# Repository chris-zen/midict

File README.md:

# midict
Hardware, firmware and software for my home made MIDI controllers

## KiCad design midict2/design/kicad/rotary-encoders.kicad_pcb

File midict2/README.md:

# MIDIct2

## Modules

### Knobs
This is a board with 8 rotary encoders to allow controlling several parameters simultaneously.

### Screen

A TFT HVGA 480x320 3.2" screen to show status to the user.
It will be controlled from software through some protocol MIDI SysEx / OSC.

### Control

This is a board with 2 rotary encoders and 6 buttons.
For controlling pages, devices, parameters, transport, ...

## Roadmap

**Knobs**

- [x] PCB design, assembly and verification
- [ ] Firmware development for the RPi
- [ ] RPi setup: mDNS, AppleMIDI driver, USB-OTG MIDI, ...

**Screen**

- [ ] MIDI/OSC Protocol to control the screen content
- [ ] Firmware to draw the screen from the RPi

**Control**

- [ ] PCB design, assembly and verification
- [ ] Firmware development for the RPi

## Images

* [First try for the rotary encoders with a photosensible dry film that was full of scratches](https://goo.gl/photos/vFz5QZcYP5DqDy86A)
* [Second try with tonner transfer using sheets from a magazinne](https://goo.gl/photos/Drio2UvwJJE7scSj7)
* [My own UV insolator](https://goo.gl/photos/k7TKoiVqc2WFZSGJ9)

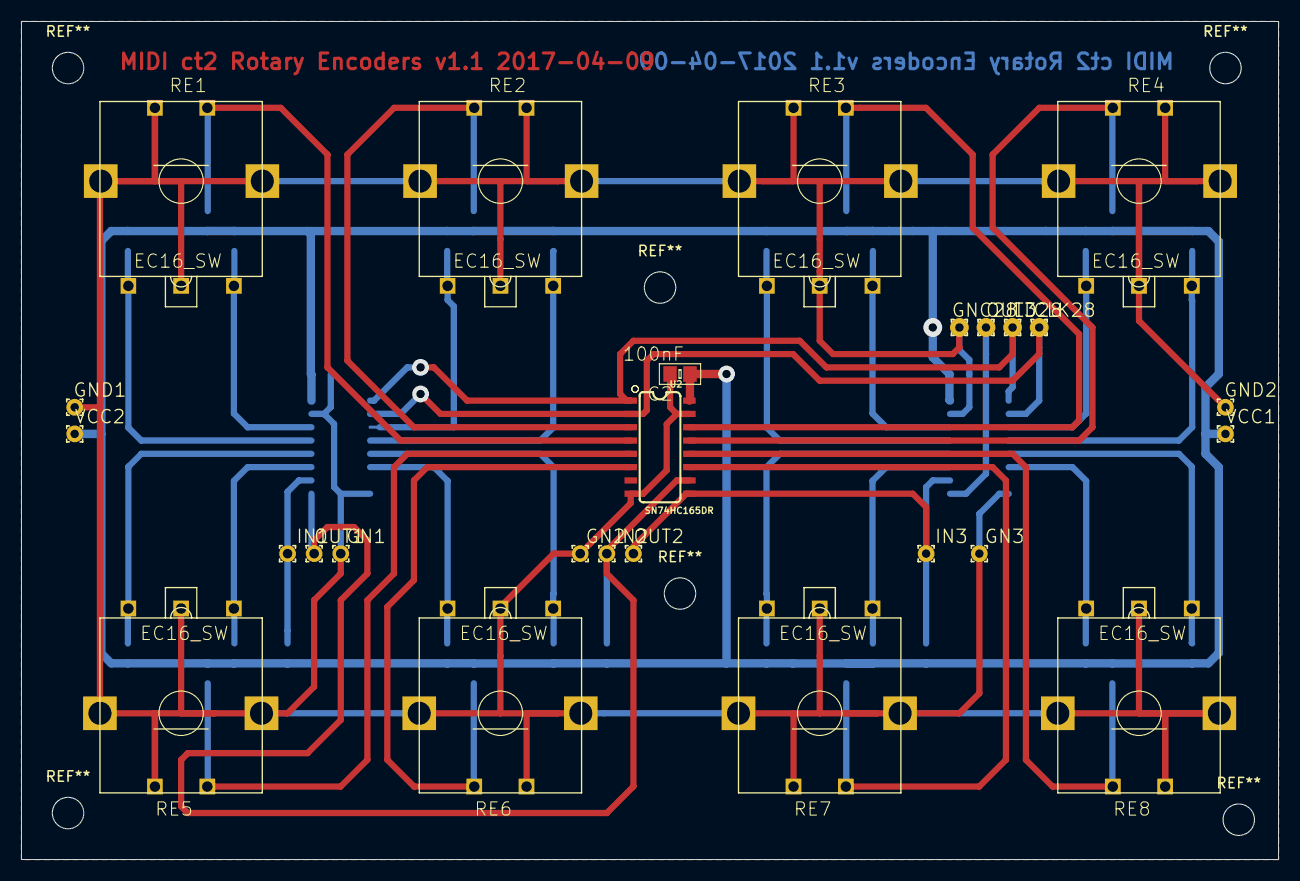
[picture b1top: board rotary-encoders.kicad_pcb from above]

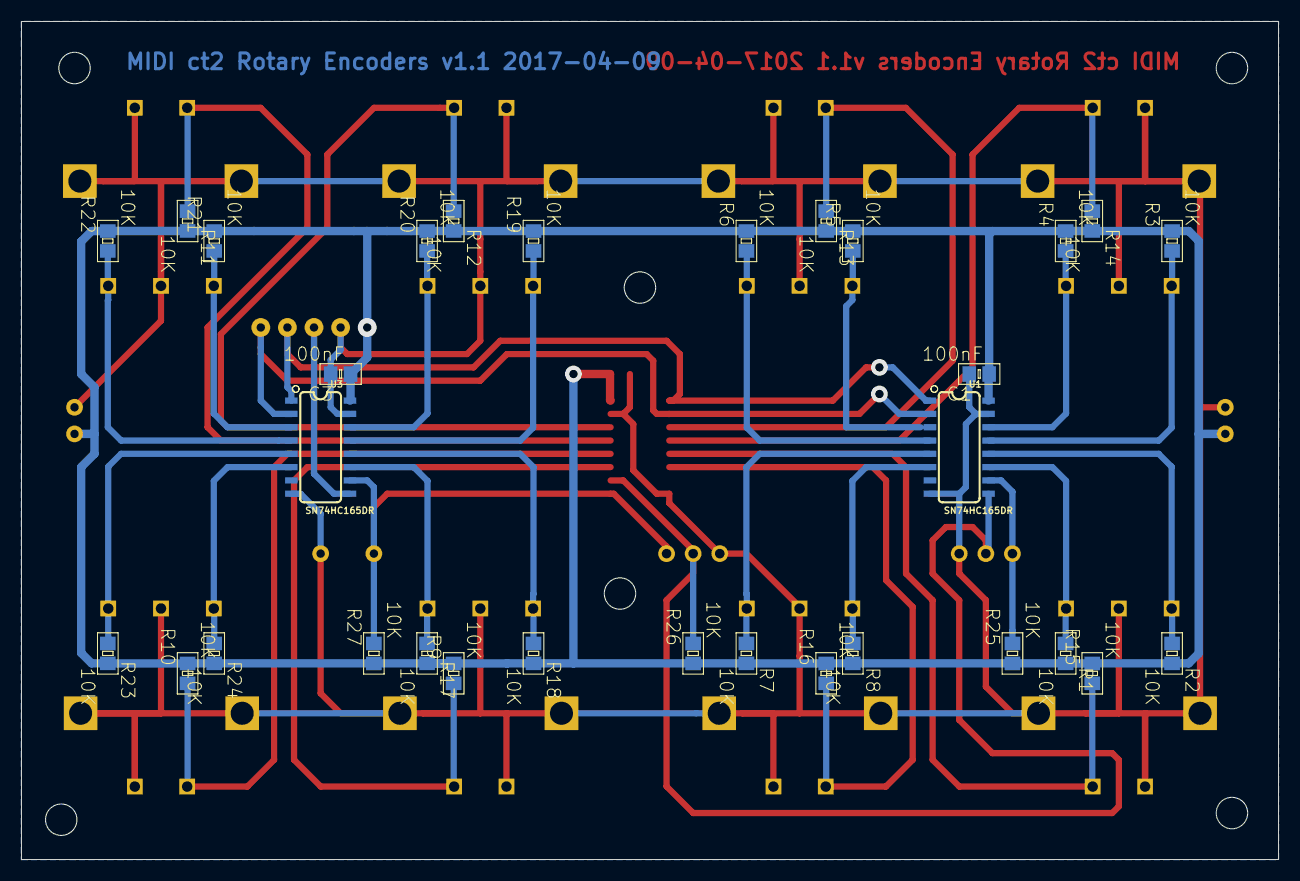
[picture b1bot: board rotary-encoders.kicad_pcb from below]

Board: 2 copper layers, 120.0 x 80.0 mm, 57 parts (31 on the bottom side), 32 nets.

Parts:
C1, C2, C3: 100nF; C0805
CLK28: 1_6_0_9
GN1, GN2, GN3: 1_6_0_9
GNC28: 1_6_0_9
GND1, GND2: 1_6_0_9
IN1, IN2, IN3: 1_6_0_9
LD28: 1_6_0_9
OUT1, OUT2, OUT3: 1_6_0_9
R1, R2, R3, R4, R5, R6, R7, R8, R9, R10, R11, R12, R13, R14, R15, R16, R17, R18, R19, R20, R21, R22, R23, R24, R25, R26, R27: 10K; R0805
RE1, RE2, RE3, RE4, RE5, RE6, RE7, RE8: EC16_SW
U1, U2, U3: SN74HC165DR; SO16
VCC1, VCC2: 1_6_0_9

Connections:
/CLK: CLK28.1, U1.2, U2.2, U3.2
/IN1: IN1.1, R25.2, U1.10
/IN2: IN2.1, OUT1.1, R26.2, U1.9, U2.10
/IN3: IN3.1, OUT2.1, R27.2, U2.9, U3.10
/LD: LD28.1, U1.1, U2.1, U3.1
/OUT3: OUT3.1, U3.9
/RE1A: R3.1, RE1.A, U1.13
/RE1B: R4.1, RE1.B, U1.14
/RE2A: R5.1, RE2.A, U1.3
/RE2B: R6.1, RE2.B, U1.4
/RE3A: R19.1, RE3.A, U3.13
/RE3B: R20.1, RE3.B, U3.14
/RE4A: R21.1, RE4.A, U3.3
/RE4B: R22.1, RE4.B, U3.4
/RE5A: R1.1, RE5.A, U1.11
/RE5B: R2.1, RE5.B, U1.12
/RE6A: R7.1, RE6.A, U1.5
/RE6B: R8.1, RE6.B, U1.6
/RE7A: R17.1, RE7.A, U3.11
/RE7B: R18.1, RE7.B, U3.12
/RE8A: R23.1, RE8.A, U3.5
/RE8B: R24.1, RE8.B, U3.6
/SW1: R14.1, RE1.E, U2.4
/SW2: R13.1, RE2.D, U2.3
/SW3: R12.1, RE3.E, U2.14
/SW4: R11.1, RE4.D, U2.13
/SW5: R15.1, RE5.D, U2.5
/SW6: R16.1, RE6.E, U2.6
/SW7: R9.1, RE7.D, U2.11
/SW8: R10.1, RE8.E, U2.12
GND: C1.2, C2.2, C3.2, GN1.1, GN2.1, GN3.1, GNC28.1, GND1.1, GND2.1, RE1.C, RE1.D, RE1.GND1, RE1.GND2, RE2.C, RE2.E, RE2.GND1, RE2.GND2, RE3.C, RE3.D, RE3.GND1, RE3.GND2, RE4.C, RE4.E, RE4.GND1, RE4.GND2, RE5.C, RE5.E, RE5.GND1, RE5.GND2, RE6.C, RE6.D, RE6.GND1, RE6.GND2, RE7.C, RE7.E, RE7.GND1, RE7.GND2, RE8.C, RE8.D, RE8.GND1, RE8.GND2, U1.8, U1.15, U2.8, U2.15, U3.8, U3.15
VCC: C1.1, C2.1, C3.1, R1.2, R2.2, R3.2, R4.2, R5.2, R6.2, R7.2, R8.2, R9.2, R10.2, R11.2, R12.2, R13.2, R14.2, R15.2, R16.2, R17.2, R18.2, R19.2, R20.2, R21.2, R22.2, R23.2, R24.2, R25.1, R26.1, R27.1, U1.16, U2.16, U3.16, VCC1.1, VCC2.1

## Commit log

2016-12-12 Initial ESP prototype
2016-12-12 Added initial work on the software side
2017-03-09 Eagle design and initial firmware prototype
2017-04-09 midict2 rotary encoders build and verified
2022-11-08 Update info
